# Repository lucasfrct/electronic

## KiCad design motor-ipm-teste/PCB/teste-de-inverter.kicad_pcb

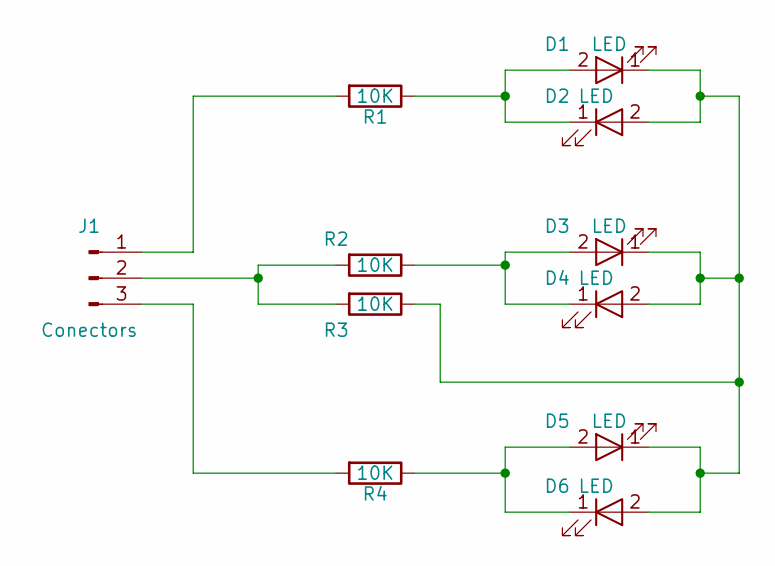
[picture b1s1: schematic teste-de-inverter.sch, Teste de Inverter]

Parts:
D1, D2, D3, D4, D5, D6: LED; LED_D10.0mm
J1: Conectors; JST_EH_B03B-EH-A_03x2.50mm_Straight
R1, R2, R3, R4: 10K; R_Axial_DIN0204_L3.6mm_D1.6mm_P5.08mm_Horizontal

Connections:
unnamed: D1.1 (K), D2.2 (A), D3.1 (K), D4.2 (A), D5.1 (K), D6.2 (A), R3.1
unnamed: D1.2 (A), D2.1 (K), R1.1
unnamed: D3.2 (A), D4.1 (K), R2.1
unnamed: D5.2 (A), D6.1 (K), R4.1
unnamed: J1.1, R1.2
unnamed: J1.2, R2.2, R3.2
unnamed: J1.3, R4.2

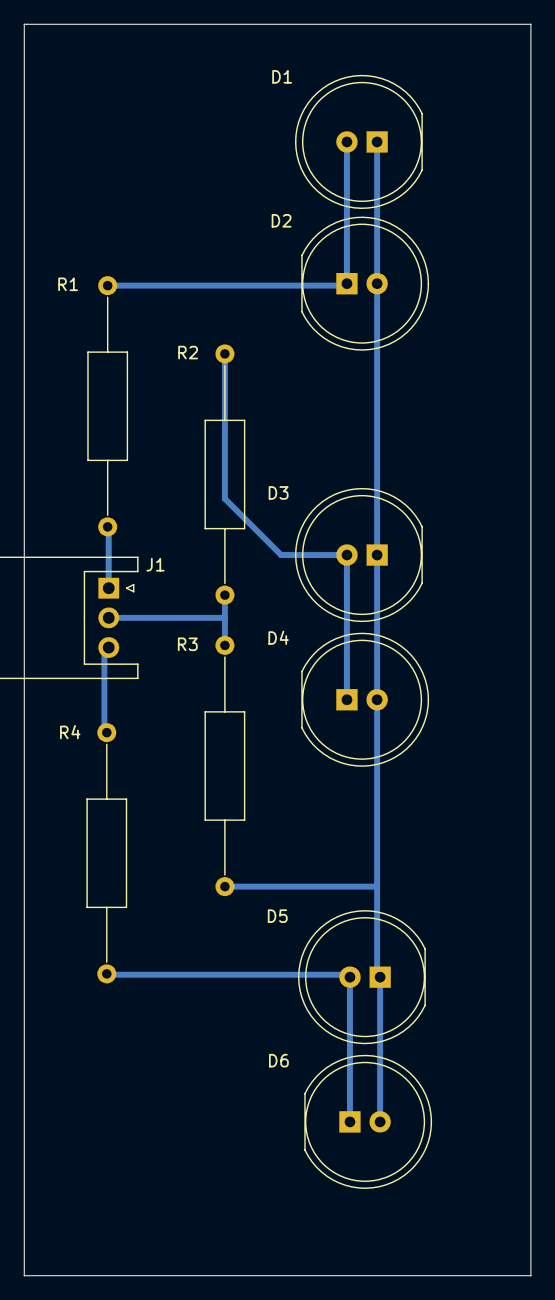
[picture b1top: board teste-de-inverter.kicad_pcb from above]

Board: 2 copper layers, 42.7 x 105.4 mm, 11 parts (0 on the bottom side), 7 nets.

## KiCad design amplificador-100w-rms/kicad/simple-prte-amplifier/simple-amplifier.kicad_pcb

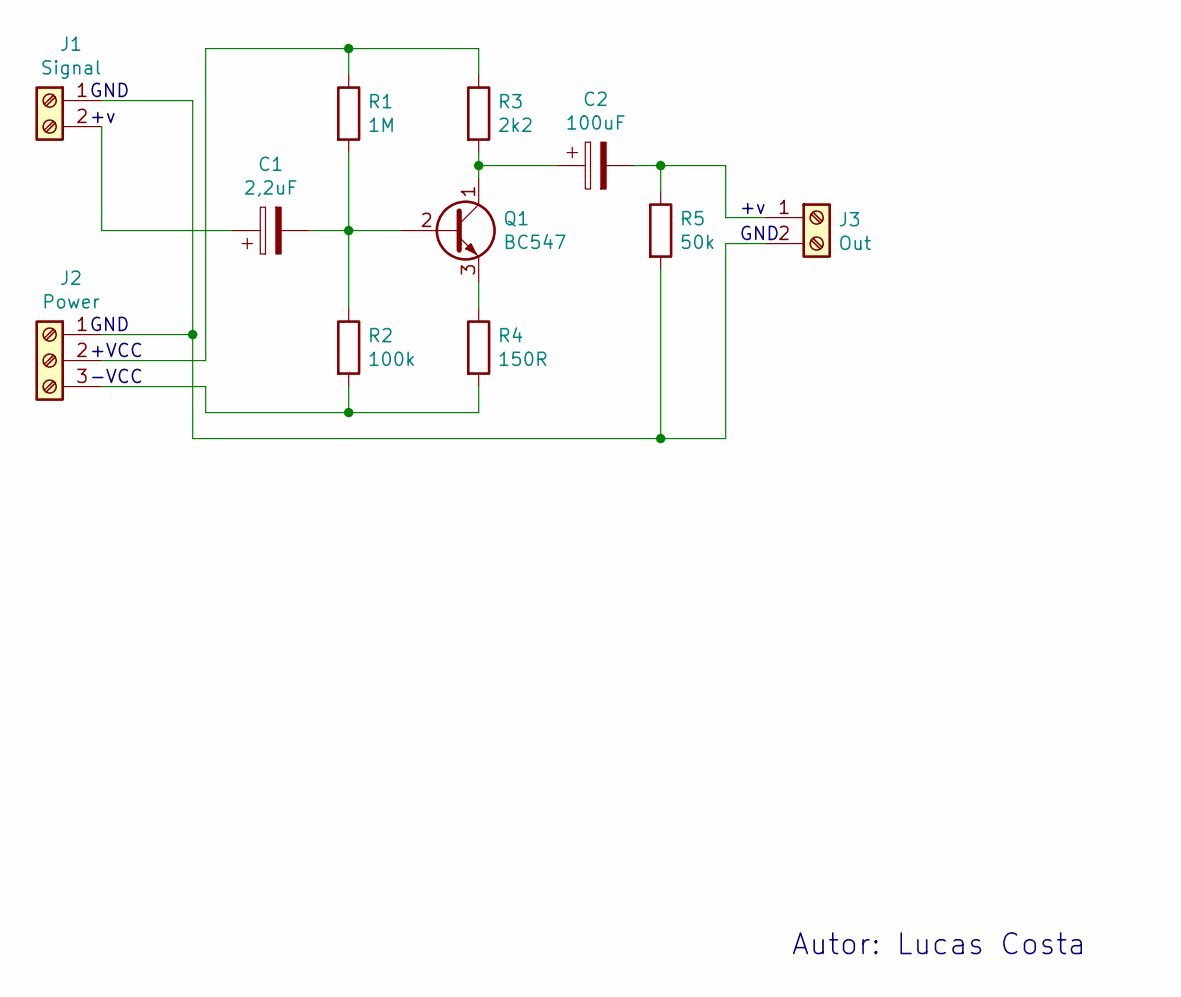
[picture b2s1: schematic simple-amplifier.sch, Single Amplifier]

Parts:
C1: 2,2uF; CP_Radial_D4.0mm_P2.00mm
C2: 100uF; CP_Radial_D4.0mm_P2.00mm
J1: Signal; JST_EH_B2B-EH-A_1x02_P2.50mm_Vertical
J2: Power; JST_EH_B3B-EH-A_1x03_P2.50mm_Vertical
J3: Out; JST_EH_B2B-EH-A_1x02_P2.50mm_Vertical
Q1: BC547; TO-92_Inline
R1: 1M; R_Axial_DIN0207_L6.3mm_D2.5mm_P10.16mm_Horizontal
R2: 100k; R_Axial_DIN0207_L6.3mm_D2.5mm_P10.16mm_Horizontal
R3: 2k2; R_Axial_DIN0207_L6.3mm_D2.5mm_P10.16mm_Horizontal
R4: 150R; R_Axial_DIN0207_L6.3mm_D2.5mm_P10.16mm_Horizontal
R5: 50k; R_Axial_DIN0207_L6.3mm_D2.5mm_P10.16mm_Horizontal

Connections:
unnamed: C1.1, J1.2
unnamed: C1.2, Q1.2 (B), R1.2, R2.1
unnamed: C2.1, Q1.1 (C), R3.2
unnamed: C2.2, J3.1, R5.1
unnamed: J1.1, J2.1, J3.2, R5.2
unnamed: J2.2, R1.1, R3.1
unnamed: J2.3, R2.2, R4.2
unnamed: Q1.3 (E), R4.1

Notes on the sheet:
GND
+VCC
-VCC
Autor: Lucas Costa

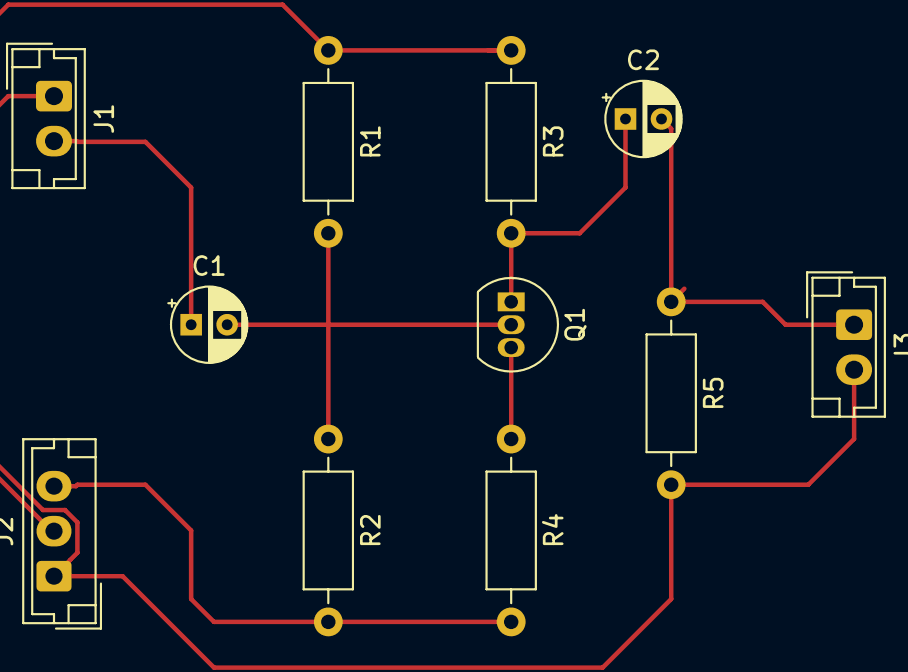
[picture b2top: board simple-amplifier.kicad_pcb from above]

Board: 2 copper layers, 11 parts (0 on the bottom side), 8 nets.
